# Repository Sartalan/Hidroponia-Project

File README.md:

# Hidroponia - Project 
## Proyecto
"Hidroponia - Project" Es un proyecto creado por la empresa ficticia "Wolfsrudel" (Integrantes en el pie de página), y consiste básicamente de una Hidroponia completamente monitoreada, con todo lo que ello conlleva; Sensores, Protocolos de comunicación, Servidores, Linux y... *mucho código*.

Nuestro proyecto consistirá de un circuito que controlará un número indeterminado de sensores *-aún-* y se encargará de enviarselos a una Raspberry Pi.
Dicha Raspberry alojará un servidor web (nginx) debido a que utilizamos un software Open Source llamado *MyCodo* el cuál es una aplicación web ligada a su propia base de datos (influxDB) quién alojará los datos para mostrarlos en pantalla para manipularlos/monitorearlos; y también servirá como una API y Endpoint para poder enviarle los datos de monitoreo a una aplicación de celular creada con React Native. Dicha aplicación mandará una *request* al servidor y éste le devolverá una *response* con los datos que la app solicitará en formato *JSON*. Todo utilizando el protocolo de comunicación wifi **HTTP**. 

Básicamente, nuestro objetivo es *automatizar y monitorear* toda magnitud física imprescindible de una Hidroponia.  

### Sobre el Repositorio 

El repositorio consta de 3 ramales principales:
1. **main**
   + Es donde se añadirá todo lo correspondiente al Hardware; Circuitos, Simulaciones, Modelos 3D e inclusive el propio código de los microcontroladores.
2. **App**
   + Es donde se desarrollará la aplicación de celular paso por paso.
3. **Web**
   + Es donde se desarrollará la aplicación web paso por paso.   
3. **Blog-Deploy**
   + Es donde se alojará toda la documentación en producción de nuestro proyecto en *órden crónologico*. Puede ser importante sí se quiere imitar nuestro proyecto; Hay diversas anotaciones que no estarán en el informe final al no necesitar un seguimiento en éste.
  
El detalle del funcionamiento de cada partes se encuentra **en su mismo ramal**.
Sí busca entender su funcionamiento a mayor profundidad **lea su propio README**

### Sobre **Wolfsrudel**

Wolfsrudel es una empresa *ficticia* creada por nosotros a pedido de la materia. Realmente somos un grupo de tres estudiantes de 7° año que buscan aprobar una materia. Así que se asumirá el rol con la seriedad la cual se espera de nosotros, motivo por el cual, en parte: creamos toda una documentación del desarrollo de nuestro proyecto, la cual en ciertas ocasiones pierde seriedad; la experiencia de hacer un proyecto de tal magnitud *requiere diversión* y nosotros defendemos esas ideas.

### Somos 

1. Barrera Alan 
2. Fariña Jorge
3. Dominguez Gabriel

Todos alumnos de 7°3° Electrónica | Año: 2024

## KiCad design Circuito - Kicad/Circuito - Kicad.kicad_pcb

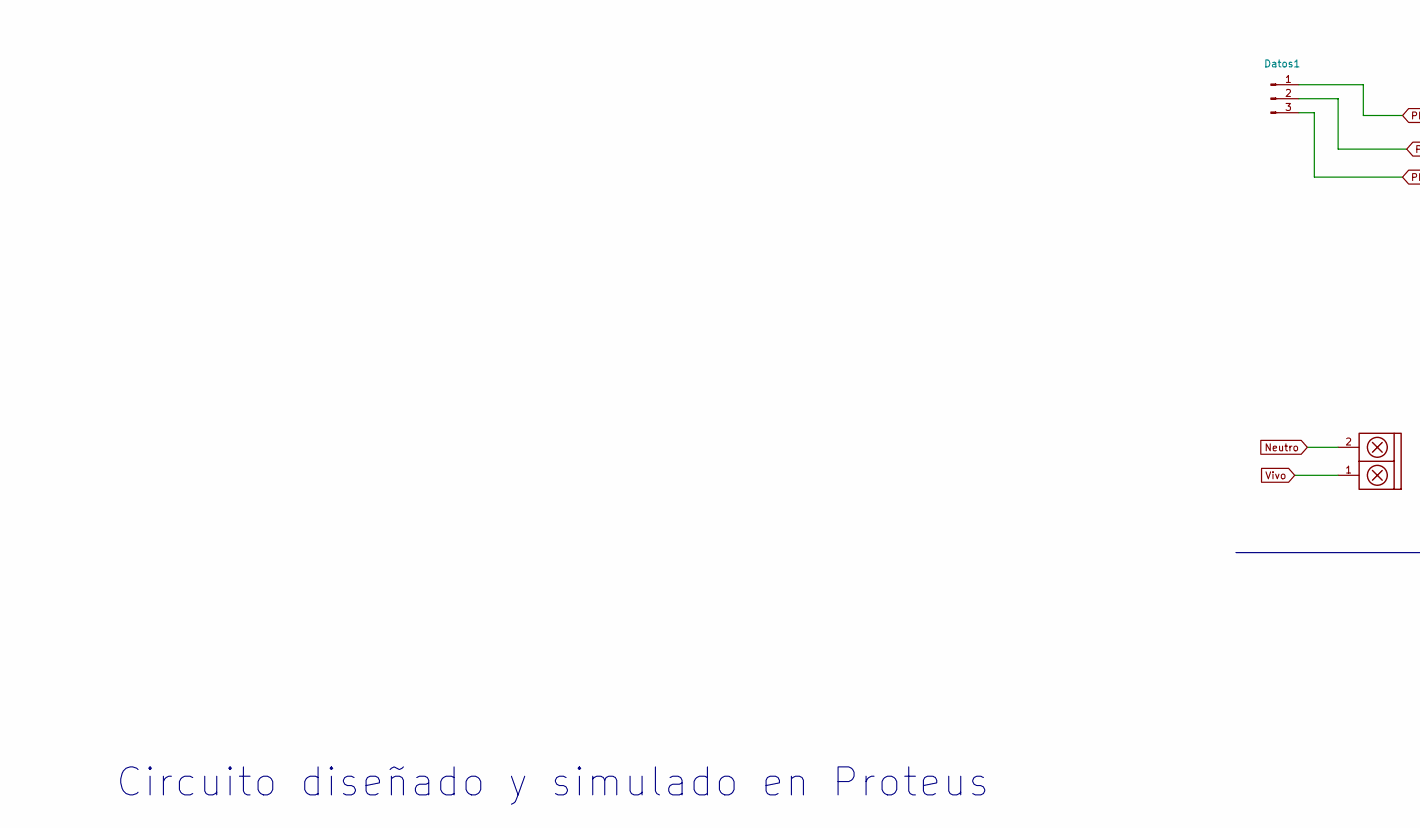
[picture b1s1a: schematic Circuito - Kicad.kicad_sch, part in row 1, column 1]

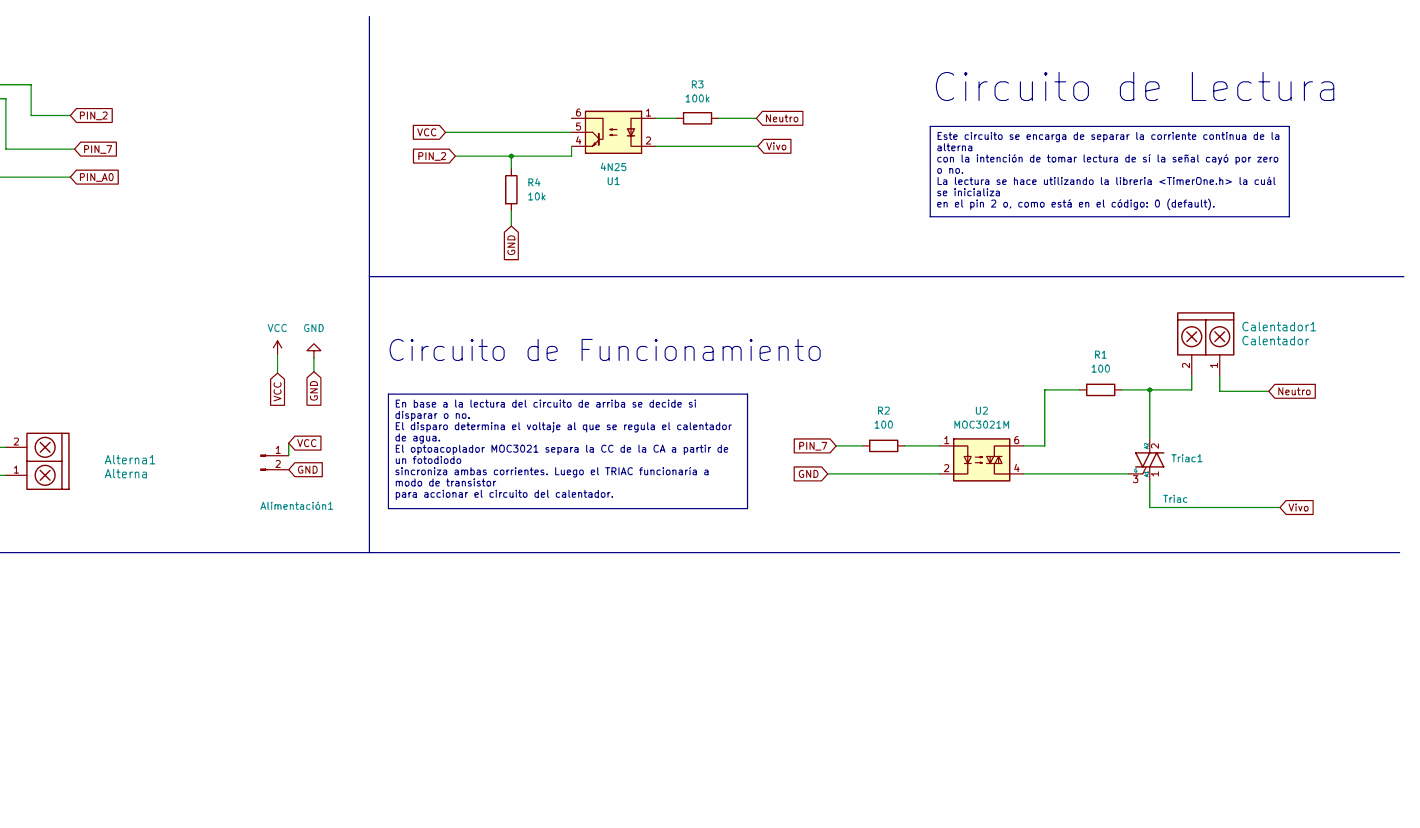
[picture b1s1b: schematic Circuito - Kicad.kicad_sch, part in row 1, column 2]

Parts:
Alimentación1: Alimentación | Arduino; Pin_Header_2
Alterna1: Alterna; BORNERA2
Calentador1: Calentador; BORNERA2
Datos1: Datos; Pin_Header_3
R1, R2: 100; R_Axial_DIN0207_L6.3mm_D2.5mm_P10.16mm_Horizontal
R3: 100k; R_Axial_DIN0207_L6.3mm_D2.5mm_P10.16mm_Horizontal
R4: 10k; R_Axial_DIN0207_L6.3mm_D2.5mm_P10.16mm_Horizontal
Triac1: Triac; TO255P1040X460X1975-3
U1: 4N25; DIP-6_W7.62mm
U2: MOC3021M; DIP762W45P254L889H508Q6

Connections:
GND: Alimentación1.2, R4.2, U2.2
unnamed: R1.2, U2.6
unnamed: R2.1, U2.1
unnamed: R3.2, U1.1
unnamed: Calentador1.2, R1.1, Triac1.2 (A2)
unnamed: Triac1.3 (G), U2.4
Neutro: Alterna1.2, Calentador1.1, R3.1
PIN_2: Datos1.1, R4.1, U1.4
PIN_7: Datos1.2, R2.2
PIN_A0: Datos1.3
VCC: Alimentación1.1, U1.5
Vivo: Alterna1.1, Triac1.1 (A1), U1.2

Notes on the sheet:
En base a la lectura del circuito de arriba se decide si disparar o no. El disparo determina el voltaje al que se regula el calentador de agua. El optoacoplador MOC3021 separa la CC de la CA a partir de un fotodiodo sincroniza ambas corrientes. Luego el TRIAC funcionaría a modo de transistor para a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
Este circuito se encarga de separar la corriente continua de la alterna con la intención de tomar lectura de sí la señal cayó por zero o no. La lectura se hace utilizando la libreria <TimerOne.h> la cuál se inicializa en el pin 2 o, como está en el código: 0 (default).
Circuito diseñado y simulado en Proteus
Circuito de Lectura
Circuito de Funcionamiento

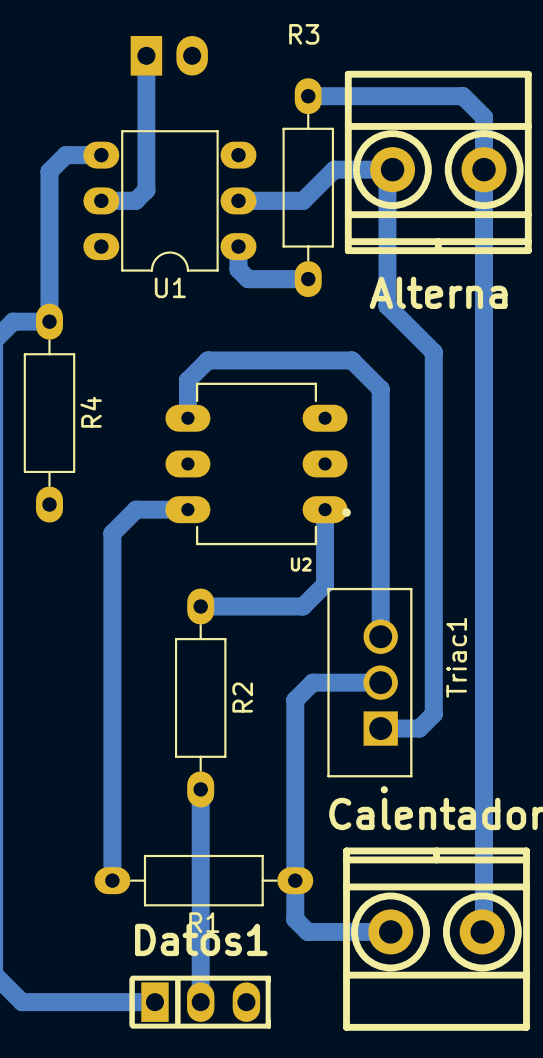
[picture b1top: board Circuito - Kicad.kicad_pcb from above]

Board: 2 copper layers, 11 parts (1 on the bottom side), 11 nets.

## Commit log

2024-08-08 Proteus Circuit && Code
2024-08-13 Circuit improvement
2024-08-13 KiCad - Circuit Improvement
2024-08-13 Nothing
2024-08-13 KiCad Circuit Improvement
2024-08-13 KiCad Improvement | Again
2024-08-13 LIbrary Added
2024-08-16 Kicad | PCB Improvement
2024-08-19 Code Improvement | Temperature Sensor
2024-08-19 Code Improvement | Functions.h
2024-08-19 Code Explained | End
2024-08-19 Readme Improvement
2024-08-19 Readme Improvement | Again
2024-08-19 Readme Improvement | Again Again EEE
2024-08-19 Code Improvement | Testeo del Sensor Funcional
2024-08-19 Math's Explained | LaTeX
2024-08-19 Math's Explained | LaTeX | Again
2024-08-19 Code Explained |T | Again
2024-08-19 Kicad | PCB Added
2024-08-19 Kicad Improvement | Wolfsrudel Logo Added
2024-08-19 Kicad Improvement | 3D Model's Added
2024-08-19 Model's Added
2024-08-20 PCB Improvement
2024-08-20 Datasheet's Added
2024-08-21 Flowchart Added
2024-08-21 Flowchart Addedn't
2024-08-21 Flowchart Added | Again (My bad)
2024-08-21 Kicad Improvement
2024-08-23 Kicad | Schematic Improvement
2024-08-23 Kicad | PCB Improvement | 6x3,5
2024-08-24 Blog | First Commit && Fork
2024-08-24 Web Improvement | v0.1
2024-08-24 Readme Improved
2024-08-24 App | First Commit
2024-08-26 Gantt Diagram Colors Improvement | Again
2024-08-26 Gantt Diagram Colors Improvement
2024-08-26 Gantt Diagram Improvement
2024-08-26 Gantt Improvement
2024-08-26 Gantt Stylish Finished
2024-08-26 Kicad | PDF
2024-08-26 PDF | Again
2024-08-26 Branch Fixed
2024-09-01 Code | Send data to Raspberry Pi (Test)
2024-09-01 Code | Send data to Raspberry Pi (Test) | Again
2024-09-02 Blog | v0.1
2024-09-02 Blog | v0.2
2024-09-02 Blog | v0.3
2024-09-02 Blog | v0.4
2024-09-04 Blog | v0.5
2024-09-04 Blog | v0.6
2024-09-09 Blog | v0.7
2024-09-09 Blog | v0.8
2024-09-09 PCB Improvement | Sensors (+) && SMD/Double Sided Circuit
2024-09-09 PDF | PCB
2024-09-09 PDF 2
2024-09-09 Blog | v0.9
2024-09-09 Blog | v1.0
2024-09-09 Blog | v1.1
2024-09-09 Blog | v1.2
2024-09-09 Blog | Test ¿
2024-09-12 Program First Version | v0.1
2024-09-12 Code Improvement | Sensors Added
2024-09-12 Code Improvement | All Sensor's Added
2024-09-13 Blog | v1.3
2024-09-13 Blog | v1.3.5
2024-09-17 Code Improvement | Python Data Filter for MyCodo
2024-09-19 Code Improvement | MyCodo Communication Finalized
2024-09-19 Blog | v1.4
2024-09-19 Code Improvement | JSON Data Added
2024-09-19 Code Improvement | Server Added
2024-09-22 App => Retorno (｡◕‿◕｡) | v2.1
2024-09-23 App => Communication Added | v2.2
2024-09-23 App => Refactored Code | v2.3
2024-09-23 App => SettingsScreen Improvement | TextInput Added | v2.4
2024-10-01 App => Code | v2.5
2024-10-01 Code Really Improved n.n
2024-10-02 Code Improvement | MyCodo Script Added
2024-10-02 Code Improvement | Sense Hat Lectures Added
2024-10-03 Code Improvement
2024-10-03 Code Improvement [C++] | Pretty Code
2024-10-03 Code Improvement [Arduino] | Water Pump with Interval (5s)
2024-10-04 Code Improvement [Python Server] | IP Lectures to send to the Sense Hat
2024-10-04 Code Improvement [Server Python] | Sense Hat Logo Added (And IP e.e)
2024-10-05 Code Improvement [Arduino] | Water pump trigger working | yay (｡◕‿◕｡)
2024-10-14 Code Improvement [Arduino]
2024-10-15 App => README}
2024-10-16 App => README
2024-10-16 Code Improvement [Python] | Send LIGHT_ON/OFF vía usb serial
2024-10-16 README
2024-10-17 Web First Commit
2024-10-17 Web Second Commit
2024-10-17 Web => Retorno (｡◕‿◕｡) | v1.2
2024-10-17 Web => Details | v1.2.5
2024-10-20 Web => Redux Implementation | v1.3
2024-10-20 Code Improvement (Python) | Bugs Solucionados (FUNCIONA)
2024-10-20 Code Improvement | Sense Hat Working && Logos Added (Kirby (｡◕‿◕｡))
2024-10-29 Code Improvement (Python && Arduino) | Send && Receive Data Serial Working (─‿‿─)
2024-10-29 Blog | v1.6
2024-10-29 Blog | v1.6.1
2024-11-02 Code Improvement [Python] | Send data through serial based on local time
2024-11-04 Code Improvement | Hidroponia Working
2024-11-04 Code Improvement | Again
2024-11-05 Code Improvement | Bomb && Lamp Working with serial data
2024-11-06 Code Improvement | Caudal Added
2024-11-06 Code Improvement | Bomb Working with Caudal-Temperature-Humidity Sensors working Correctly
2024-11-06 FUNCIONA TODO EN EL COLE (｡◕‿◕｡)
2024-11-11 Informe | v1.7
2024-11-11 Informe | v1.7.1
2024-11-11 Informe | v1.7.5
2024-11-13 Code Bug Resolved | Water Pump Working on his own
2024-11-13 Water Pump Working | Again
2024-11-13 Code Improvement | Bash Init File.sh
2024-11-13 Code Improvement | All Working
2024-11-14 Informe | v1.7.8
2024-11-14 Code Improvement | YF-S201 Working
2024-11-14 Code Improvement | Logo's Inverted
2024-11-14 Informe | v1.8
2024-11-15 Informe | v1.8.5
2024-11-15 Informe | v1.8.1
2024-11-15 Informe | v1.8.6
2024-11-22 App => Code | v2.6
2024-11-23 Informe S. De Control | v1.8.9
2024-11-26 Web => Responsive Design | v1.4
2024-11-26 Web => Fetch && First Server Communication | v1.5
2024-11-26 Web => Details | v1.5.1
2024-11-26 Informe S. de Control | v1.9
2024-11-26 Informe S. de Control | v1.9.1
2024-11-27 Informe Proyecto | v1.9.5
2024-11-27 Informe del Proyecto Finalizado | v2.0 (｡◕‿◕｡)
2024-11-27 Web => Server Communication with global State | Redux | v1.6
